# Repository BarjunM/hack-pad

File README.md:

# The DM’s Grimoire

The **DM’s Grimoire** is a D&D **macropad** built for Dungeon Masters to control their campaigns. With 9 mechanical keys, an OLED display, RGB lighting, and a custom spellbook‑style enclosure, this device becomes a physical “grimoire” of power for any tabletop roleplaying game.

---

## Why I Made This

As a long‑time Dungeon enjoyer and the permanent dungeon master (no thanks to my friends), I wanted something that was extremely functional — I wanted it to feel like an artifact from the game world itself. Instead of clicking around with a mouse, now I press a button and summon a thunderstorm… or a dragon roar.

---

## Project Photos

### Front View  

### Back View  

---

## Key Orientation Screenshot

The 3D‑printed case was modeled in Onshape for a 3x3 matrix.

---

## Wiring Diagram / Schematic

Here’s the schematic for all switches, OLED, and RGB integration:

---

## PCB Screenshot

Designed using KiCad and printed through Hack Club’s parts inventory.

---

## Assembly & Build Photos

Soldering, population, and final enclosure fit.

---

## BOM
9x Cherry MX Switches
9x Blank DSA Keycaps
4x M3x5x4 Heatset inserts
4x M3x16mm SHCS Bolts
1x 0.91 inch OLED displays (Max 1x)
1x EC11 Rotary Encoder
1x XIAO RP2040
1x Case (2 printed parts)
1x Custom PCB

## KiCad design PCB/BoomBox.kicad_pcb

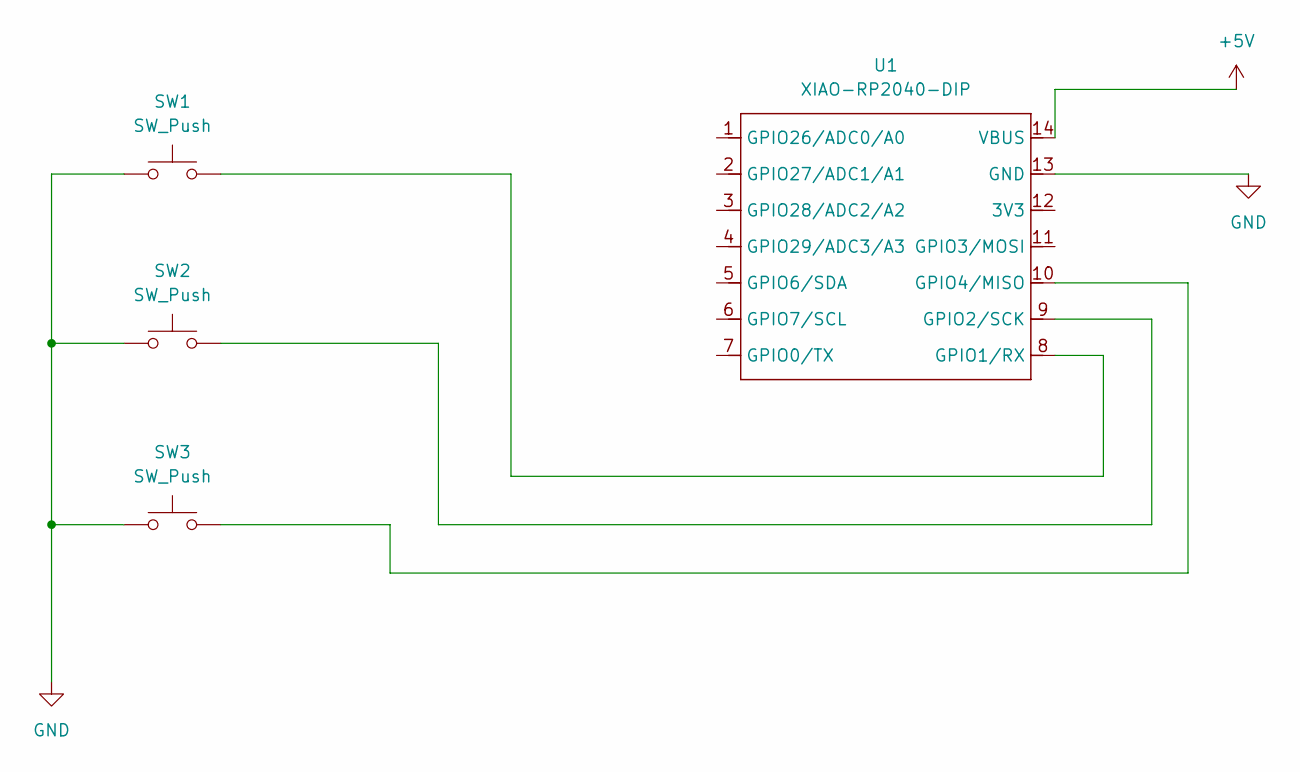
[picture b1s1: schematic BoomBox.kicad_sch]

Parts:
SW1, SW2, SW3: SW_Push; SW_Cherry_MX_1.00u_PCB
U1: XIAO-RP2040-DIP

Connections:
+5V: U1.14 (VBUS)
GND: SW1.1, SW2.1, SW3.1, U1.13 (GND)
unnamed: SW1.2, U1.8 (GPIO1/RX)
unnamed: SW2.2, U1.9 (GPIO2/SCK)
unnamed: SW3.2, U1.10 (GPIO4/MISO)

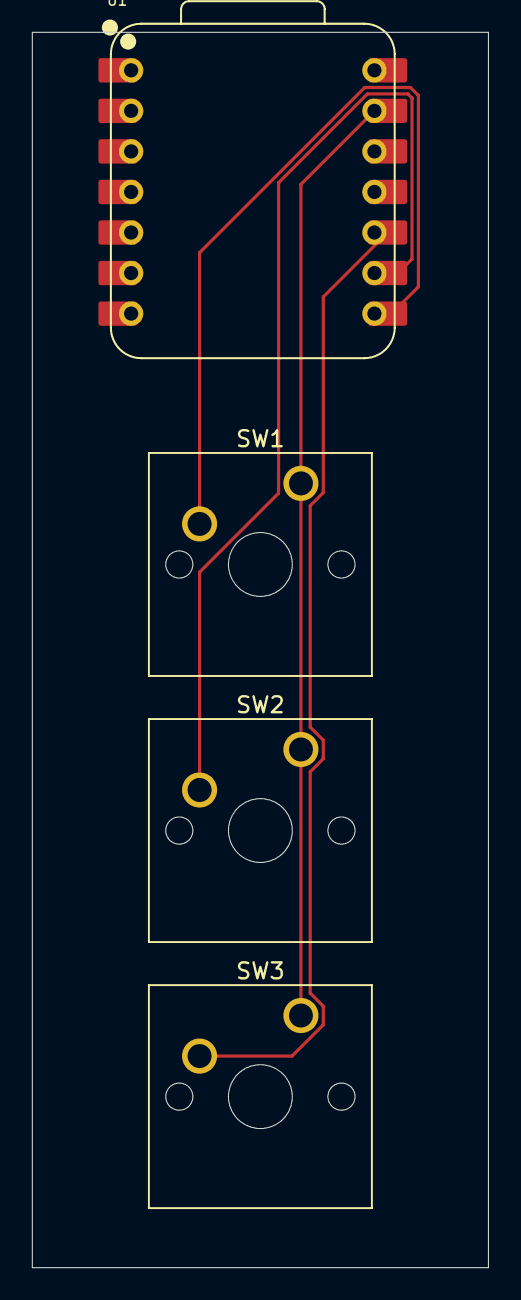
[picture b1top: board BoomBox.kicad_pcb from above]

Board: 2 copper layers, 28.6 x 77.4 mm, 4 parts (0 on the bottom side), 4 nets.

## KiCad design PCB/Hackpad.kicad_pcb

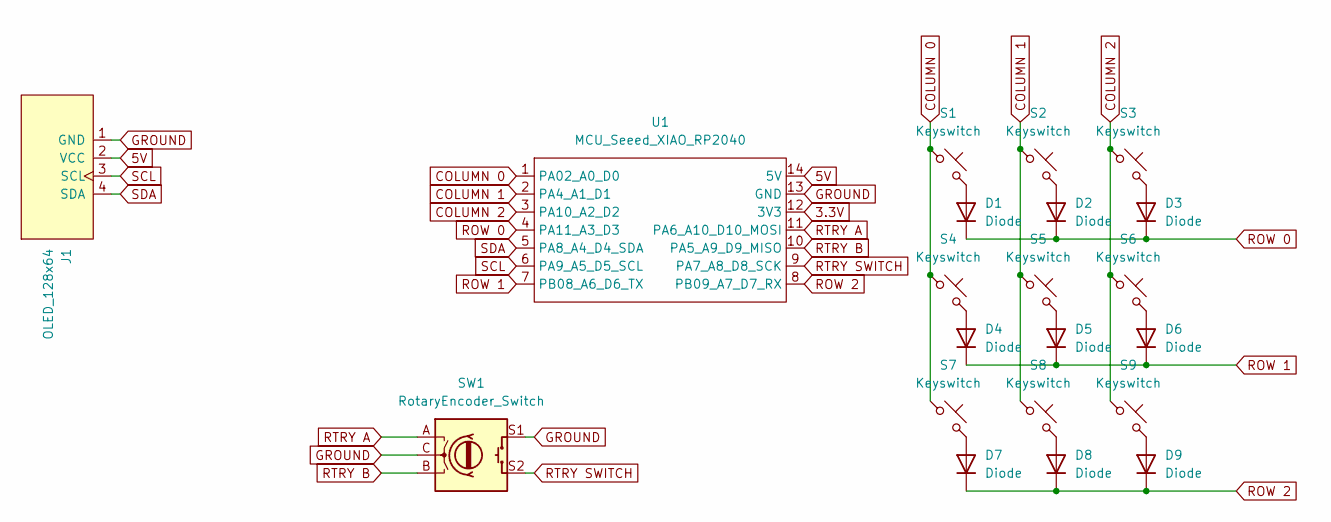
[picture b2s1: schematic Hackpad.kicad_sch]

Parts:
D1, D2, D3, D4, D5, D6, D7, D8, D9: Diode; Diode_DO-35
J1: OLED_128x64
S1, S2, S3, S4, S5, S6, S7, S8, S9: Keyswitch; MX_PCB_1.00u
SW1: RotaryEncoder_Switch; RotaryEncoder_Alps_EC11E-Switch_Vertical_H20mm
U1: MCU_Seeed_XIAO_RP2040; Seeed_XIAO_RP2040

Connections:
3.3V: U1.12 (3V3)
5V: J1.2 (VCC), U1.14 (5V)
COLUMN 0: S1.1, S4.1, S7.1, U1.1 (PA02_A0_D0)
COLUMN 1: S2.1, S5.1, S8.1, U1.2 (PA4_A1_D1)
COLUMN 2: S3.1, S6.1, S9.1, U1.3 (PA10_A2_D2)
GROUND: J1.1 (GND), SW1.C, SW1.S1, U1.13 (GND)
unnamed: D1.2 (A), S1.2
unnamed: D2.2 (A), S2.2
unnamed: D3.2 (A), S3.2
unnamed: D4.2 (A), S4.2
unnamed: D5.2 (A), S5.2
unnamed: D6.2 (A), S6.2
unnamed: D7.2 (A), S7.2
unnamed: D8.2 (A), S8.2
unnamed: D9.2 (A), S9.2
ROW 0: D1.1 (K), D2.1 (K), D3.1 (K), U1.4 (PA11_A3_D3)
ROW 1: D4.1 (K), D5.1 (K), D6.1 (K), U1.7 (PB08_A6_D6_TX)
ROW 2: D7.1 (K), D8.1 (K), D9.1 (K), U1.8 (PB09_A7_D7_RX)
RTRY A: SW1.A, U1.11 (PA6_A10_D10_MOSI)
RTRY B: SW1.B, U1.10 (PA5_A9_D9_MISO)
RTRY SWITCH: SW1.S2, U1.9 (PA7_A8_D8_SCK)
SCL: J1.3 (SCL), U1.6 (PA9_A5_D5_SCL)
SDA: J1.4 (SDA), U1.5 (PA8_A4_D4_SDA)

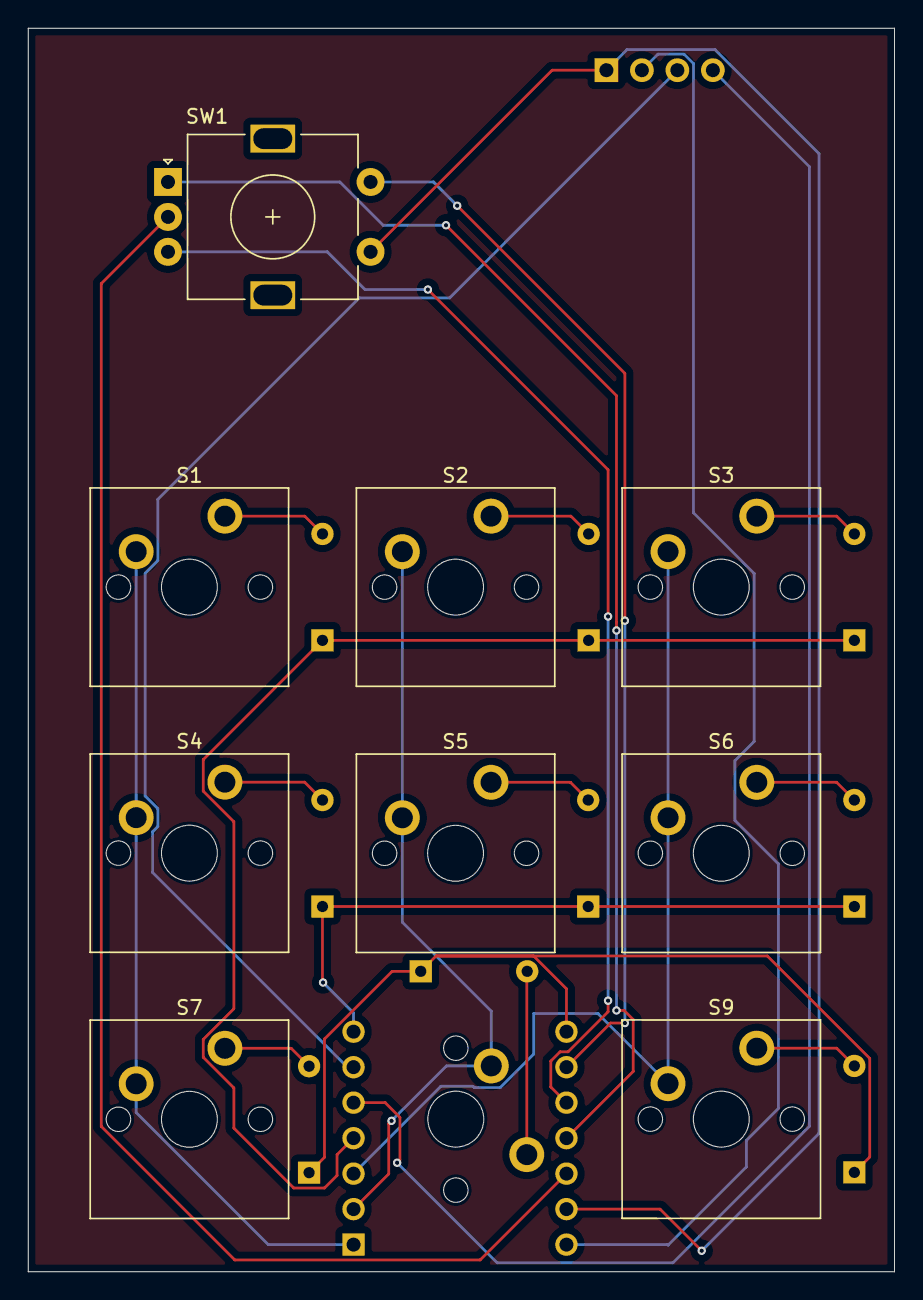
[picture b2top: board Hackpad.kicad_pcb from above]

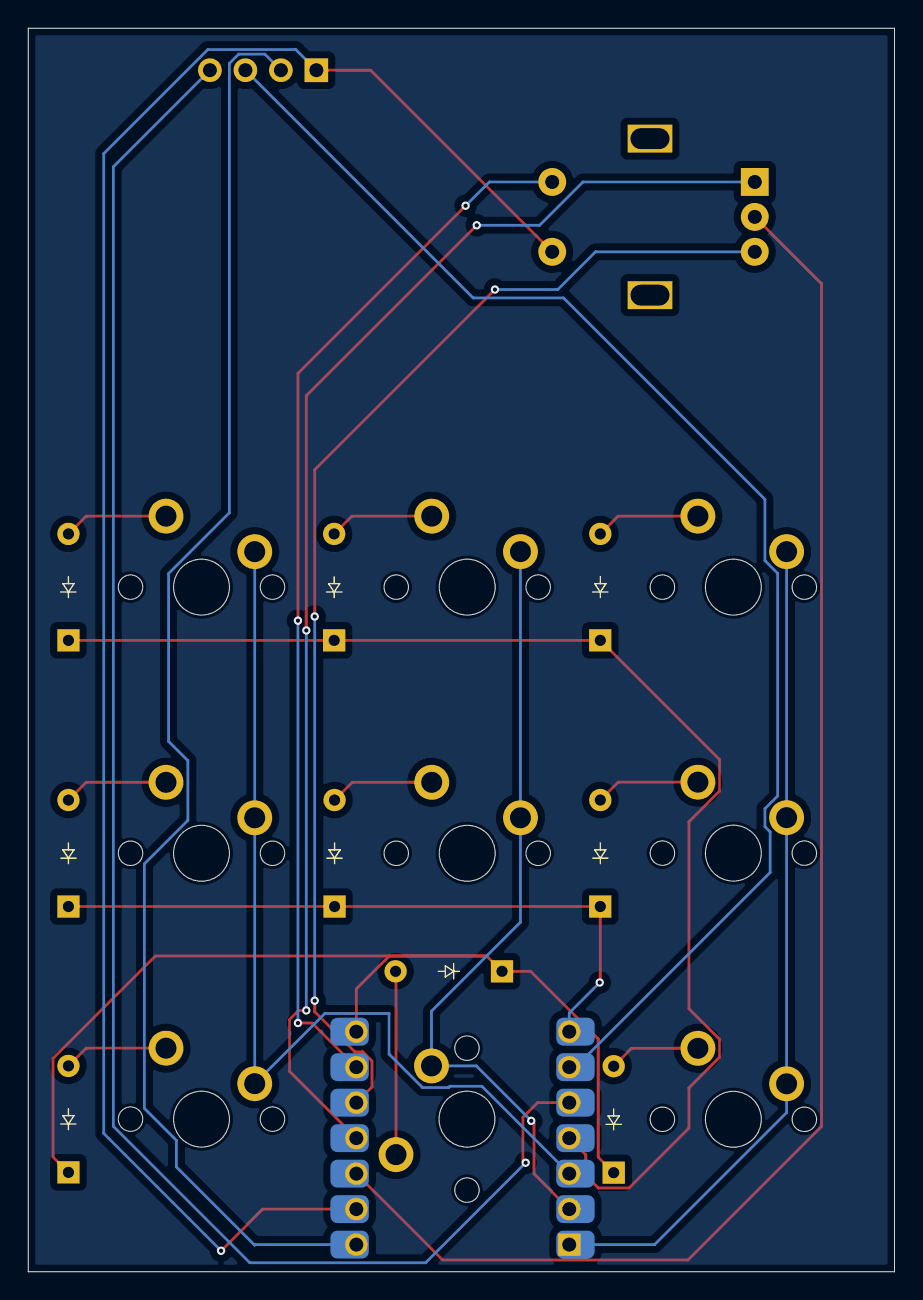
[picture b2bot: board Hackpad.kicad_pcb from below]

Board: 2 copper layers, 62.0 x 89.0 mm, 21 parts (10 on the bottom side), 22 nets.

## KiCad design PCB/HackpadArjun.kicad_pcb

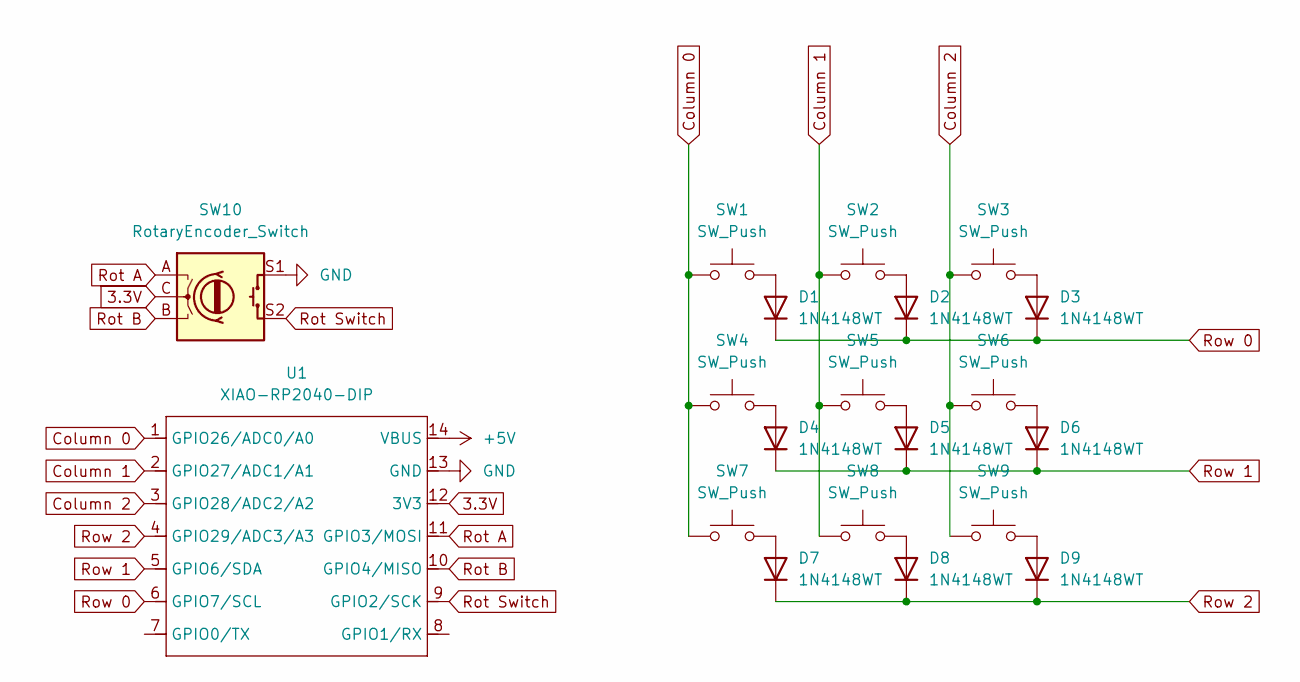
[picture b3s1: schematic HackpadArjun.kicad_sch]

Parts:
D1, D2, D3, D4, D5, D6, D7, D8, D9: 1N4148WT; D_DO-35_SOD27_P7.62mm_Horizontal
SW1, SW2, SW3, SW4, SW5, SW6, SW7, SW8, SW9: SW_Push; SW_Cherry_MX_1.00u_PCB
SW10: RotaryEncoder_Switch; RotaryEncoder_Alps_EC11E-Switch_Vertical_H20mm_MountingHoles
U1: XIAO-RP2040-DIP

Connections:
3.3V: SW10.C, U1.12 (3V3)
+5V: U1.14 (VBUS)
Column 0: SW1.1, SW4.1, SW7.1, U1.1 (GPIO26/ADC0/A0)
Column 1: SW2.1, SW5.1, SW8.1, U1.2 (GPIO27/ADC1/A1)
Column 2: SW3.1, SW6.1, SW9.1, U1.3 (GPIO28/ADC2/A2)
GND: SW10.S1, U1.13 (GND)
unnamed: D1.2 (A), SW1.2
unnamed: D2.2 (A), SW2.2
unnamed: D3.2 (A), SW3.2
unnamed: D4.2 (A), SW4.2
unnamed: D5.2 (A), SW5.2
unnamed: D6.2 (A), SW6.2
unnamed: D7.2 (A), SW7.2
unnamed: D8.2 (A), SW8.2
unnamed: D9.2 (A), SW9.2
Rot A: SW10.A, U1.11 (GPIO3/MOSI)
Rot B: SW10.B, U1.10 (GPIO4/MISO)
Rot Switch: SW10.S2, U1.9 (GPIO2/SCK)
Row 0: D1.1 (K), D2.1 (K), D3.1 (K), U1.6 (GPIO7/SCL)
Row 1: D4.1 (K), D5.1 (K), D6.1 (K), U1.5 (GPIO6/SDA)
Row 2: D7.1 (K), D8.1 (K), D9.1 (K), U1.4 (GPIO29/ADC3/A3)

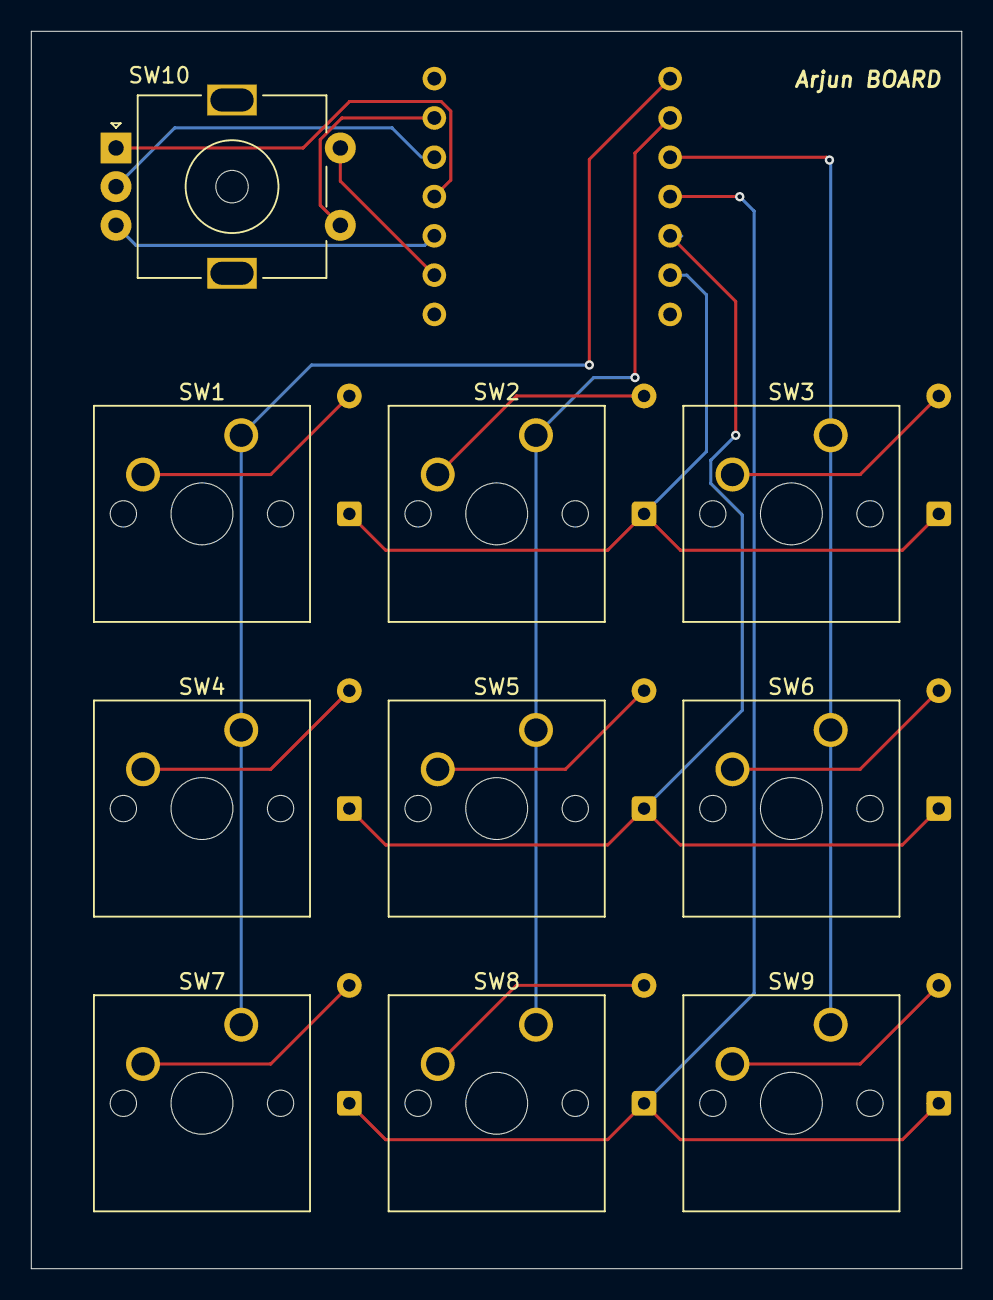
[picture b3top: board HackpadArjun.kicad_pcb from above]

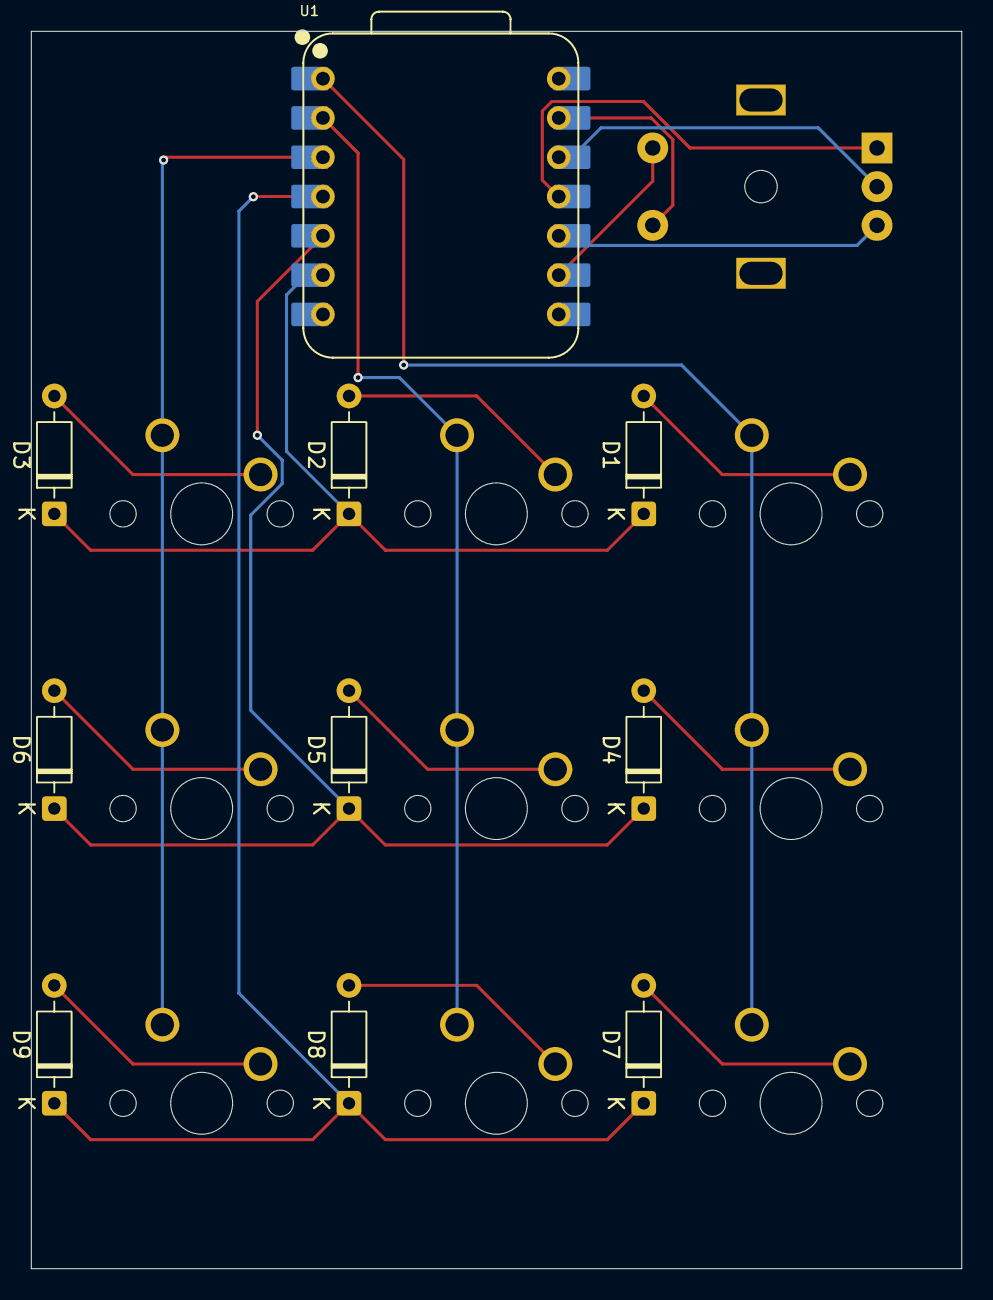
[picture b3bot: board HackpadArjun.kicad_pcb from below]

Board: 2 copper layers, 60.1 x 80.0 mm, 20 parts (10 on the bottom side), 20 nets.

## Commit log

2025-07-01 updated pcb + fixed cad
2025-07-02 Added README and initial files
2025-07-02 Rename README.me to README.md
2025-07-02 Overwrite main branch with local files
2025-07-02 add/fix prod stuff
2025-07-02 Updated Image Files
2025-07-02 Updated Image Files v2
2025-07-02 Updated Image Files v3
2025-07-02 Updated Image Files v4
2025-08-15 just updated
